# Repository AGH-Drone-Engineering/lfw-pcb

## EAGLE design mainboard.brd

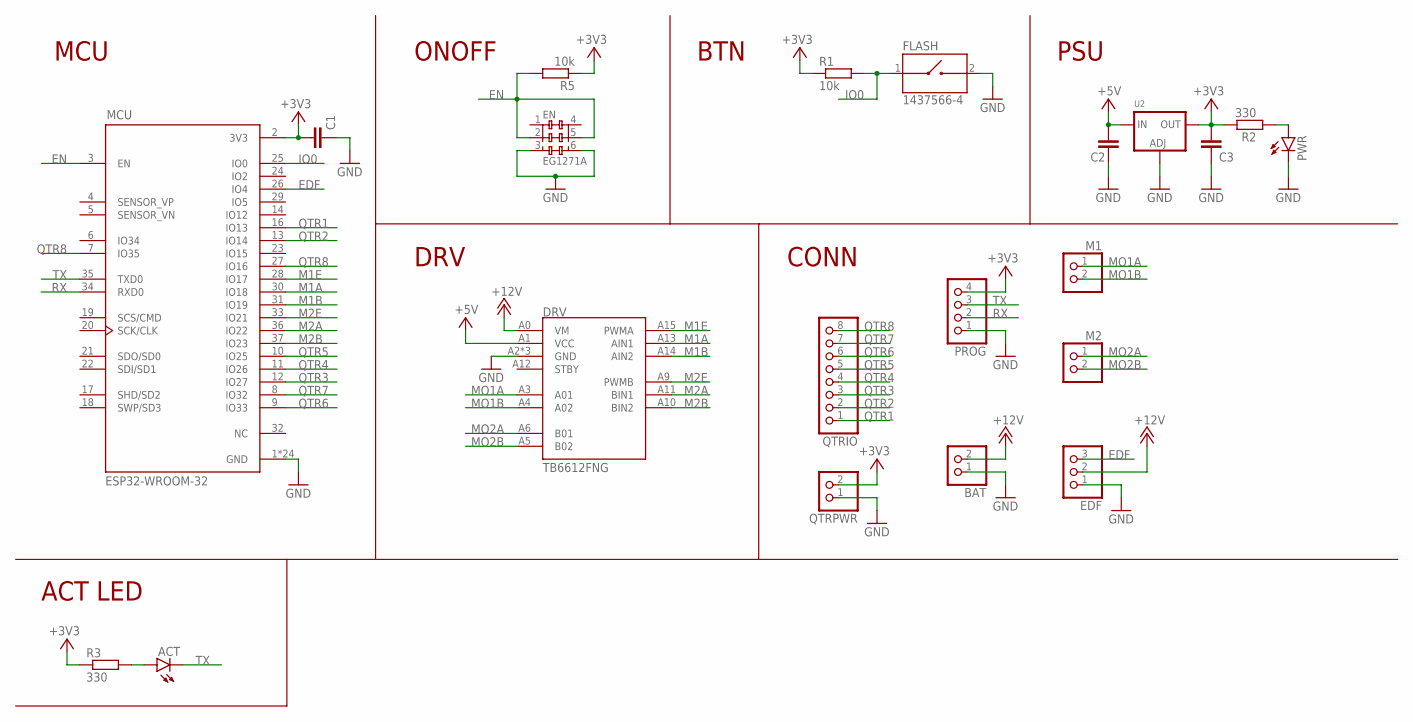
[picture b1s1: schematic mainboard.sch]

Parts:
ACT: LEDCHIPLED_0805; CHIPLED_0805
BAT: PINHD-1X2; 1X02
C1, C2, C3: C-EUC0805; C0805
DRV: TB6612FNG
EDF: PINHD-1X3; 1X03
EN: EG1271A; SW_EG1271A
FLASH: 1437566-4; SW_1437566-4
M1, M2: PINHD-1X2; 1X02
MCU: ESP32-WROOM-32; MODULE_ESP32-WROOM-32
PROG: PINHD-1X4; 1X04
PWR: LEDCHIPLED_0805; CHIPLED_0805
QTRIO: PINHD-1X8; 1X08
QTRPWR: PINHD-1X2; 1X02
R1, R5: 10k; R0603
R2, R3: 330; R0603
U2: LM1117SOT223-WAVE; SOT223-W

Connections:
+3V3: C1.1, C3.1, MCU.2 (3V3), PROG.4, QTRPWR.2, R1.1, R2.2, R3.1, R5.1, U2.2 (OUT)
+5V: C2.1, DRV.A1 (VCC), U2.3 (IN)
+12V: BAT.2, DRV.A0 (VM), EDF.2
EDF: EDF.3, MCU.26 (IO4)
EN: EN.2, EN.5, MCU.3 (EN), R5.2
GND: BAT.1, C1.2, C2.2, C3.2, DRV.A2 (GND), DRV.A7 (GND), DRV.A8 (GND), EDF.1, EN.3, EN.6, FLASH.2, MCU.1 (GND), MCU.15 (GND), MCU.38 (GND), MCU.39_1 (GND), MCU.39_2 (GND), MCU.39_3 (GND), MCU.39_4 (GND), MCU.39_5 (GND), MCU.39_6 (GND), MCU.39_7 (GND), MCU.39_8 (GND), MCU.39_9 (GND), MCU.39_10 (GND), MCU.39_11 (GND), MCU.39_12 (GND), MCU.39_13 (GND), MCU.39_14 (GND), MCU.39_15 (GND), MCU.39_16 (GND), MCU.39_17 (GND), MCU.39_18 (GND), MCU.39_19 (GND), MCU.39_20 (GND), MCU.39_21 (GND), PROG.1, PWR.C, QTRPWR.1, U2.1 (ADJ)
IO0: FLASH.1, MCU.25 (IO0), R1.2
M1A: DRV.A13 (AIN1), MCU.30 (IO18)
M1B: DRV.A14 (AIN2), MCU.31 (IO19)
M1E: DRV.A15 (PWMA), MCU.28 (IO17)
M2A: DRV.A11 (BIN1), MCU.36 (IO22)
M2B: DRV.A10 (BIN2), MCU.37 (IO23)
M2E: DRV.A9 (PWMB), MCU.33 (IO21)
MO1A: DRV.A3 (A01), M1.1
MO1B: DRV.A4 (A02), M1.2
MO2A: DRV.A6 (B01), M2.1
MO2B: DRV.A5 (B02), M2.2
unnamed: PWR.A, R2.1
unnamed: ACT.A, R3.2
QTR1: MCU.16 (IO13), QTRIO.1
QTR2: MCU.13 (IO14), QTRIO.2
QTR3: MCU.12 (IO27), QTRIO.3
QTR4: MCU.11 (IO26), QTRIO.4
QTR5: MCU.10 (IO25), QTRIO.5
QTR6: MCU.9 (IO33), QTRIO.6
QTR7: MCU.8 (IO32), QTRIO.7
QTR8: MCU.7 (IO35), MCU.27 (IO16), QTRIO.8
RX: MCU.34 (RXD0), PROG.2
TX: ACT.C, MCU.35 (TXD0), PROG.3

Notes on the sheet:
MCU
ONOFF
BTN
PSU
ACT LED
CONN
DRV

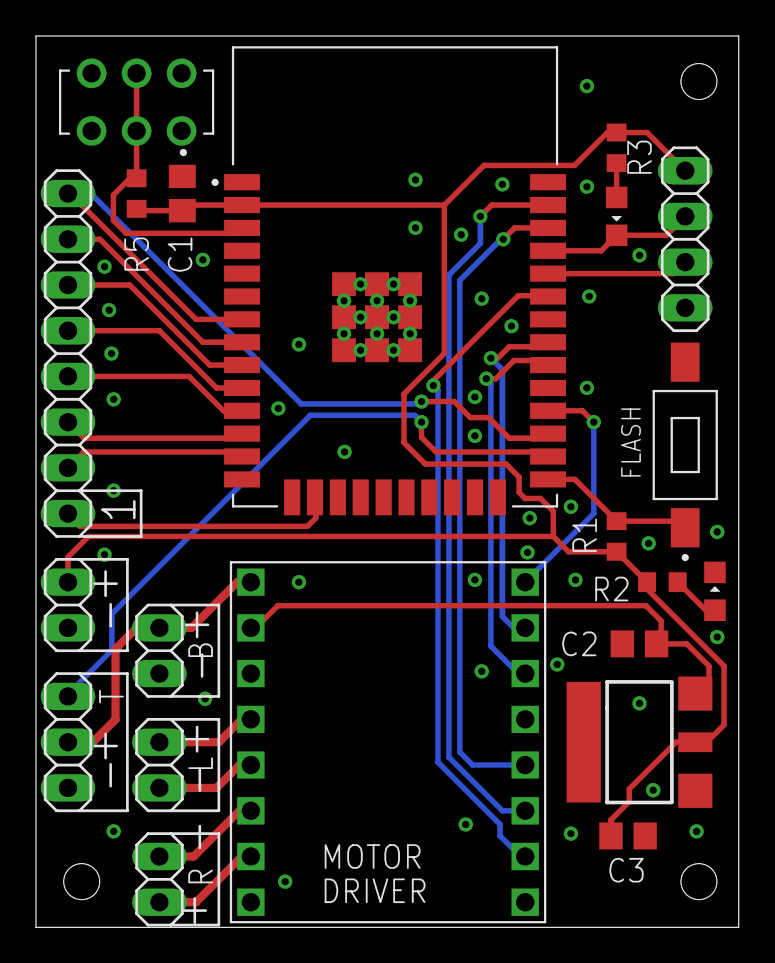
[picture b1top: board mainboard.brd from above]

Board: 2 copper layers, 39.0 x 49.5 mm, 21 parts (0 on the bottom side), 29 nets.

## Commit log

2022-10-26 rev 1

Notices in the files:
parts and their libraries:
microbuilder: This work is placed in the public domain, and may be freely used for commercial and non-commercial work with the following conditions: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
SparkFun-Aesthetics: Licensing: Creative Commons ShareAlike 4.0 International - https://creativecommons.org/licenses/by-sa/4.0
